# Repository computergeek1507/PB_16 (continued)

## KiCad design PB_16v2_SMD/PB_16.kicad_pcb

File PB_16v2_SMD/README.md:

# Copyright and Disclaimer
Copyright: Scott Hanson

This documentation describes Open Hardware and is licensed under the CERN Open Hardware License Version 2 - Strongly Reciprocal. (CERN-OHL-S)

You may redistribute and modify this documentation under the terms of the CERN OHL-S-v2 (https://ohwr.org/cern_ohl_s_v2.txt). This documentation is distributed WITHOUT ANY EXPRESS OR IMPLIED WARRANTY, INCLUDING OF MERCHANTABILITY, SATISFACTORY QUALITY AND FITNESS FOR A PARTICULAR PURPOSE. Please see the CERN OHL v2-S for applicable conditions

**Under CERN OHL-S-v2, derivative work must be publicly released as defined in subsection 3.3**

# PB 16v2

The PB 16v2 is a surface mount(SMD) version of the original PB16. The updated PB 16v2 has 16 local pixel ports, one remote receiver port(4 remote ports), a 16 port expansion, and 2 serial ports. A total of 36 pixel outputs. All the design files are open source and available on github.

### Features
* Powered by FPP Falcon Player
* Standalone/Master/Remote/Bridge Support
* 16 3-Wire Pixel Ports
* 1 RJ-45 Connector for a remote differential port.
* 700 pixel per output at 40 FPS or 1300 at 20 FPS
* 2 DMX Serial Outputs
* 1 RJ-45 Connectors with DMX/LOR Wiring Support
* Fused Powered DMX Output
* USB port for Ethernet,WIFI, or Audio
* OLED Display header
* Adafruit Real Time Clock Header Connector
* 2 pin GPIO Header for Push Button or Relay Support
* 5v - 24v Vin Support
* Expansion Header for additional 16 pixel outputs, Supports Falcon(v3) Expansion Boards

### Purchase
I (Scott) have a limited quantity of fully assembled PCB's available for purchase. PM me if interested.

## [Part BOM](https://github.com/computergeek1507/PB_16/raw/master/PB_16v2_SMD/PB_16_BOM.ods)

## [Interactive BOM](https://computergeek1507.github.io/PB_16/PB_16v2_SMD/bom/ibom)

----
## Changelog

v2.3
----
* 2026-02-09
* Switched to TSSOP-20 for U4 & U5.
* Switched Pixel Outputs to Dual 3.5mm/3.81mm Pads.
* Switched Expansion Header to 24pin Falcon V4 pinout.
* Removed OLED Slide Switch.
* Removed Top Solder pour.

v2.2
----
* 2022-06-05
* Updated 5V regulator to "Universal" footprint to support different regulators.
* Switched to 603 Resistors and Capacitors
* Added Logo

v2.1
----
* 2022-05-26
* Switched to surface mount 33ohm resistors on pixel outputs.

v2
----
* 2020-08-11 (publicly released 2022-01-22)
* First SMD version.
* Based off PB16v1.
* Used 805 Resistors and Capacitors
* Changed one RJ45 port to new differential output.
* Added Power Controller to USB port.
* Added TVS Diodes to USB port.

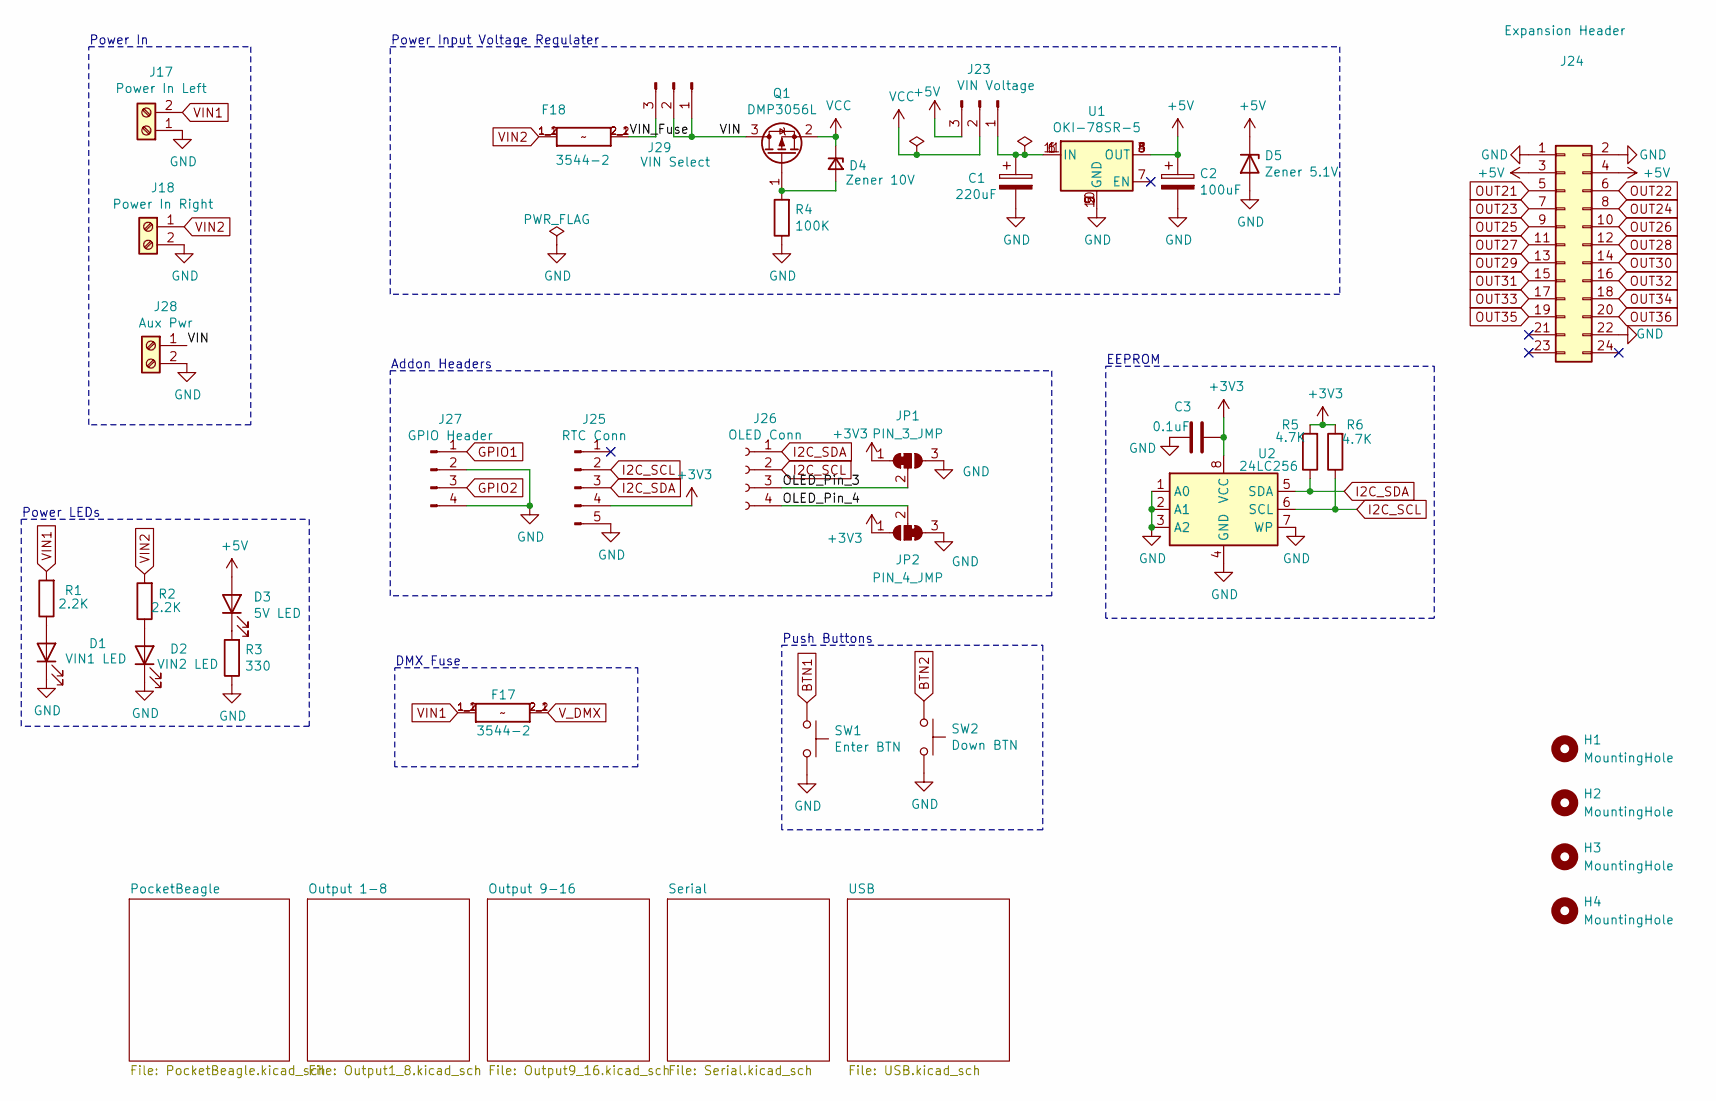
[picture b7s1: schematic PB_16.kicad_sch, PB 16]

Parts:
C1: 220uF; CP_Radial_D10.0mm_P5.00mm; MPN ECA-1HM221; Digi-Key_PN P5183-ND
C2: 100uF; CP_Elec_6.3x5.4_Nichicon; MPN UWX1C101MCL1GB; Digi-Key_PN 493-2105-1-ND
C3: 0.1uF; C_0603_1608Metric; MPN CL10B104KB8NNWC; Digi-Key_PN 1276-1935-2-ND
D1: VIN1 LED; LED_0603_1608Metric; MPN LTST-C190KRKT; Digi-Key_PN 160-1436-2-ND
D2: VIN2 LED; LED_0603_1608Metric; MPN LTST-C190KRKT; Digi-Key_PN 160-1436-2-ND
D3: 5V LED; LED_0603_1608Metric; MPN LTST-C190KRKT; Digi-Key_PN 160-1436-2-ND
D4: Zener 10V; D_SOD-123; MPN MMSZ5240B-7-F; Digi-Key_PN MMSZ5240B-FDICT-ND
D5: Zener 5.1V; D_SOD-123; MPN MMSZ5231B-7-F; Digi-Key_PN MMSZ5231B-FDICT-ND
F17, F18: 3544-2; FUSE_3544-2; MPN 3544-2; Digi-Key_PN 36-3544-2-ND
H1, H2, H3, H4: MountingHole; MountingHole_3.7mm
J17: Power In Left; BARRIER_BLOCK_1ROW_2POS_P9.5MM; MPN OSTYK51102030; Digi-Key_PN ED2953-ND
J18: Power In Right; BARRIER_BLOCK_1ROW_2POS_P9.5MM; MPN OSTYK51102030; Digi-Key_PN ED2953-ND
J23: VIN Voltage; PinHeader_1x03_P2.54mm_Vertical; MPN 61300311121; Digi-Key_PN 732-5316-ND
J24: Expansion Header; IDC-Header_2x12_P2.54mm_Vertical; MPN SBH11-PBPC-D20-ST-BK; Digi-Key_PN S9175-ND
J25: RTC Conn; PinHeader_1x05_P2.54mm_Vertical; MPN 61300511121; Digi-Key_PN 732-5318-ND
J26: OLED Conn; PinSocket_1x04_P2.54mm_Vertical; MPN PPTC041LFBN-RC; Digi-Key_PN S7002-ND
J27: GPIO Header; JST_XH_B4B-XH-A_1x04_P2.50mm_Vertical; MPN B4B-XH-A(LF)(SN); Digi-Key_PN 455-2249-ND
J28: Aux Pwr; PHOENIX_MKDS1_2-3.81; MPN 1727010; Digi-Key_PN 277-1947-ND
J29: VIN Select; PinHeader_1x03_P2.54mm_Vertical; MPN 61300311121; Digi-Key_PN 732-5316-ND
JP1: PIN_3_JMP; SolderJumper-3_P1mm_Bridged12
JP2: PIN_4_JMP; SolderJumper-3_P1mm_Bridged23
Q1: DMP3056L; SOT-23; MPN DMP3056L-7; Digi-Key_PN DMP3056L-7DICT-ND
R1, R2: 2.2K; R_0603_1608Metric; MPN RC0603FR-071KL; Digi-Key_PN 311-1.00KHRTR-ND
R3: 330; R_0603_1608Metric; MPN CRGCQ0603F120R; Digi-Key_PN A129677CT-ND
R4: 100K; R_0603_1608Metric; MPN RT0603BRD07100KL; Digi-Key_PN YAG1235CT-ND
R5, R6: 4.7K; R_0603_1608Metric; MPN RC0603JR-074K7L; Digi-Key_PN 311-4.7KGRCT-ND
SW1: Enter BTN; SW_Push_1P1T_NO_6x6mm_H9.5mm; MPN PTS645SL50SMTR92 LFS; Digi-Key_PN CKN9088CT-ND
SW2: Down BTN; SW_Push_1P1T_NO_6x6mm_H9.5mm; MPN PTS645SL50SMTR92 LFS; Digi-Key_PN CKN9088CT-ND
U1: OKI-78SR-5; Universal_5V_Horizontal; MPN OKI-78SR-5/1.5-W36-C; Digi-Key_PN 811-2196-5-ND
U2: 24LC256; SOIC-8_3.9x4.9mm_P1.27mm; MPN 24LC256T-I/SN; Digi-Key_PN 24LC256T-I/SNCT-ND

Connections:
+3V3: C3.1, J25.4, JP1.1 (A), JP2.1 (A), R5.2, R6.2, U2.8 (VCC); also elsewhere on the board
+5V: C2.1, D3.2 (A), D5.1 (K), J23.3, J24.3, J24.4, U1.3 (OUT), U1.4 (OUT), U1.8 (OUT); also elsewhere on the board
/OLED_Pin_3: J26.3, JP1.2 (C)
/OLED_Pin_4: J26.4, JP2.2 (C)
/VIN: J28.1, J29.1, J29.2, Q1.3 (D)
/VIN_Fuse: F18.2_1 (2), F18.2_2 (2), J29.3
BTN1: SW1.1; also elsewhere on the board
BTN2: SW2.1; also elsewhere on the board
GND: C1.2, C2.2, C3.2, D1.1 (K), D2.1 (K), D5.2 (A), J17.1, J18.2, J24.1, J24.2, J24.22, J25.5, J27.2, J27.4, J28.2, JP1.3 (B), JP2.3 (B), R3.1, R4.1, SW1.2, SW2.2, U1.2 (GND), U1.5 (GND), U1.9 (GND), U1.10 (GND), U2.1 (A0), U2.2 (A1), U2.3 (A2), U2.4 (GND), U2.7 (WP); also elsewhere on the board
GPIO1: J27.1; also elsewhere on the board
GPIO2: J27.3; also elsewhere on the board
I2C_SCL: J25.2, J26.2, R6.1, U2.6 (SCL); also elsewhere on the board
I2C_SDA: J25.3, J26.1, R5.1, U2.5 (SDA); also elsewhere on the board
unnamed: D1.2 (A), R1.1
unnamed: D2.2 (A), R2.1
unnamed: D3.1 (K), R3.2
unnamed: D4.2 (A), Q1.1 (G), R4.2
unnamed: C1.1, J23.1, U1.1 (IN), U1.6 (IN), U1.11 (IN)
OUT21: J24.5; also elsewhere on the board
OUT22: J24.6; also elsewhere on the board
OUT23: J24.7; also elsewhere on the board
OUT24: J24.8; also elsewhere on the board
OUT25: J24.9; also elsewhere on the board
OUT26: J24.10; also elsewhere on the board
OUT27: J24.11; also elsewhere on the board
OUT28: J24.12; also elsewhere on the board
OUT29: J24.13; also elsewhere on the board
OUT30: J24.14; also elsewhere on the board
OUT31: J24.15; also elsewhere on the board
OUT32: J24.16; also elsewhere on the board
OUT33: J24.17; also elsewhere on the board
OUT34: J24.18; also elsewhere on the board
OUT35: J24.19; also elsewhere on the board
OUT36: J24.20; also elsewhere on the board
VCC: D4.1 (K), J23.2, Q1.2 (S)
VIN1: F17.1_1 (1), F17.1_2 (1), J17.2, R1.2; also elsewhere on the board
VIN2: F18.1_1 (1), F18.1_2 (1), J18.1, R2.2; also elsewhere on the board
V_DMX: F17.2_1 (2), F17.2_2 (2); also elsewhere on the board

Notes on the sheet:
Power Input Voltage Regulater
Push Buttons
Power LEDs
EEPROM
Power In
Addon Headers
DMX Fuse

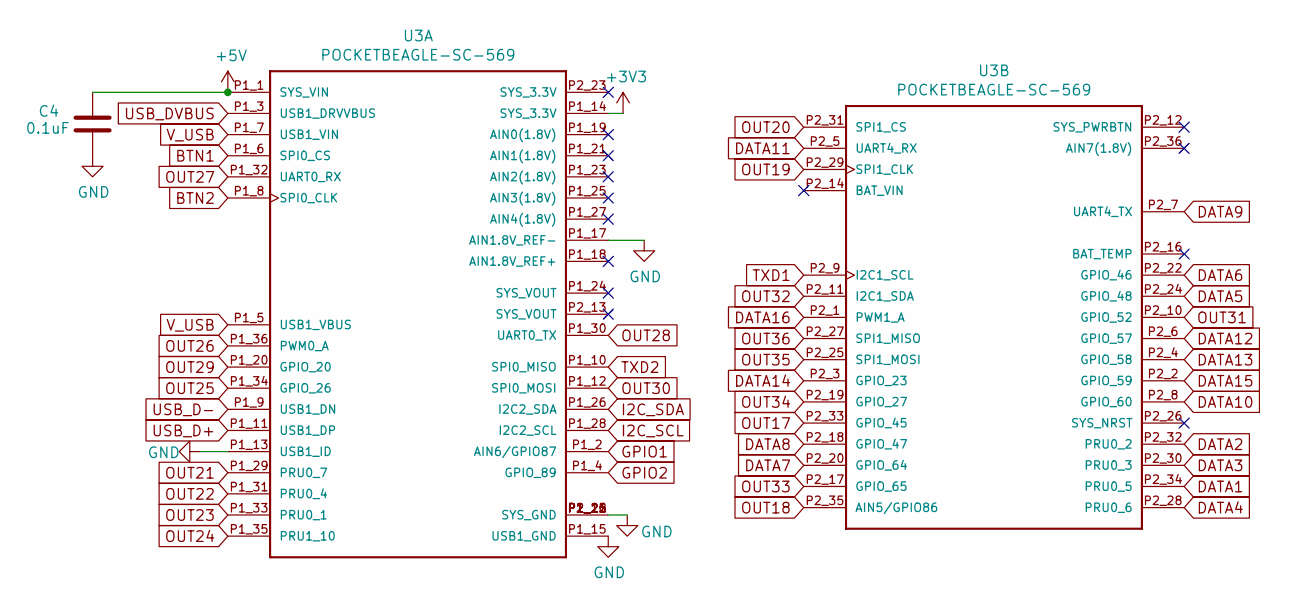
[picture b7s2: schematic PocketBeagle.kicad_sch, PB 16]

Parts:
C4: 0.1uF; C_0603_1608Metric; MPN CL10B104KB8NNWC; Digi-Key_PN 1276-1935-2-ND
U3: POCKETBEAGLE-SC-569; BEAGLE_POCKETBEAGLE-SC-569; MPN POCKETBEAGLE-SC-569; Digi-Key_PN POCKETBEAGLE-SC-569-ND

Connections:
+3V3: U3.P1_14 (SYS_3.3V); also elsewhere on the board
+5V: C4.1, U3.P1_1 (SYS_VIN); also elsewhere on the board
BTN1: U3.P1_6 (SPI0_CS); also elsewhere on the board
BTN2: U3.P1_8 (SPI0_CLK); also elsewhere on the board
DATA1: U3.P2_34 (PRU0_5); also elsewhere on the board
DATA2: U3.P2_32 (PRU0_2); also elsewhere on the board
DATA3: U3.P2_30 (PRU0_3); also elsewhere on the board
DATA4: U3.P2_28 (PRU0_6); also elsewhere on the board
DATA5: U3.P2_24 (GPIO_48); also elsewhere on the board
DATA6: U3.P2_22 (GPIO_46); also elsewhere on the board
DATA7: U3.P2_20 (GPIO_64); also elsewhere on the board
DATA8: U3.P2_18 (GPIO_47); also elsewhere on the board
DATA9: U3.P2_7 (UART4_TX); also elsewhere on the board
DATA10: U3.P2_8 (GPIO_60); also elsewhere on the board
DATA11: U3.P2_5 (UART4_RX); also elsewhere on the board
DATA12: U3.P2_6 (GPIO_57); also elsewhere on the board
DATA13: U3.P2_4 (GPIO_58); also elsewhere on the board
DATA14: U3.P2_3 (GPIO_23); also elsewhere on the board
DATA15: U3.P2_2 (GPIO_59); also elsewhere on the board
DATA16: U3.P2_1 (PWM1_A); also elsewhere on the board
GND: C4.2, U3.P1_13 (USB1_ID), U3.P1_15 (USB1_GND), U3.P1_16 (SYS_GND), U3.P1_17 (AIN1.8V_REF-), U3.P1_22 (SYS_GND), U3.P2_15 (SYS_GND), U3.P2_21 (SYS_GND); also elsewhere on the board
GPIO1: U3.P1_2 (AIN6/GPIO87); also elsewhere on the board
GPIO2: U3.P1_4 (GPIO_89); also elsewhere on the board
I2C_SCL: U3.P1_28 (I2C2_SCL); also elsewhere on the board
I2C_SDA: U3.P1_26 (I2C2_SDA); also elsewhere on the board
OUT17: U3.P2_33 (GPIO_45); also elsewhere on the board
OUT18: U3.P2_35 (AIN5/GPIO86); also elsewhere on the board
OUT19: U3.P2_29 (SPI1_CLK); also elsewhere on the board
OUT20: U3.P2_31 (SPI1_CS); also elsewhere on the board
OUT21: U3.P1_29 (PRU0_7); also elsewhere on the board
OUT22: U3.P1_31 (PRU0_4); also elsewhere on the board
OUT23: U3.P1_33 (PRU0_1); also elsewhere on the board
OUT24: U3.P1_35 (PRU1_10); also elsewhere on the board
OUT25: U3.P1_34 (GPIO_26); also elsewhere on the board
OUT26: U3.P1_36 (PWM0_A); also elsewhere on the board
OUT27: U3.P1_32 (UART0_RX); also elsewhere on the board
OUT28: U3.P1_30 (UART0_TX); also elsewhere on the board
OUT29: U3.P1_20 (GPIO_20); also elsewhere on the board
OUT30: U3.P1_12 (SPI0_MOSI); also elsewhere on the board
OUT31: U3.P2_10 (GPIO_52); also elsewhere on the board
OUT32: U3.P2_11 (I2C1_SDA); also elsewhere on the board
OUT33: U3.P2_17 (GPIO_65); also elsewhere on the board
OUT34: U3.P2_19 (GPIO_27); also elsewhere on the board
OUT35: U3.P2_25 (SPI1_MOSI); also elsewhere on the board
OUT36: U3.P2_27 (SPI1_MISO); also elsewhere on the board
TXD1: U3.P2_9 (I2C1_SCL); also elsewhere on the board
TXD2: U3.P1_10 (SPI0_MISO); also elsewhere on the board
USB_D+: U3.P1_11 (USB1_DP); also elsewhere on the board
USB_D-: U3.P1_9 (USB1_DN); also elsewhere on the board
USB_DVBUS: U3.P1_3 (USB1_DRVVBUS); also elsewhere on the board
V_USB: U3.P1_5 (USB1_VBUS), U3.P1_7 (USB1_VIN); also elsewhere on the board

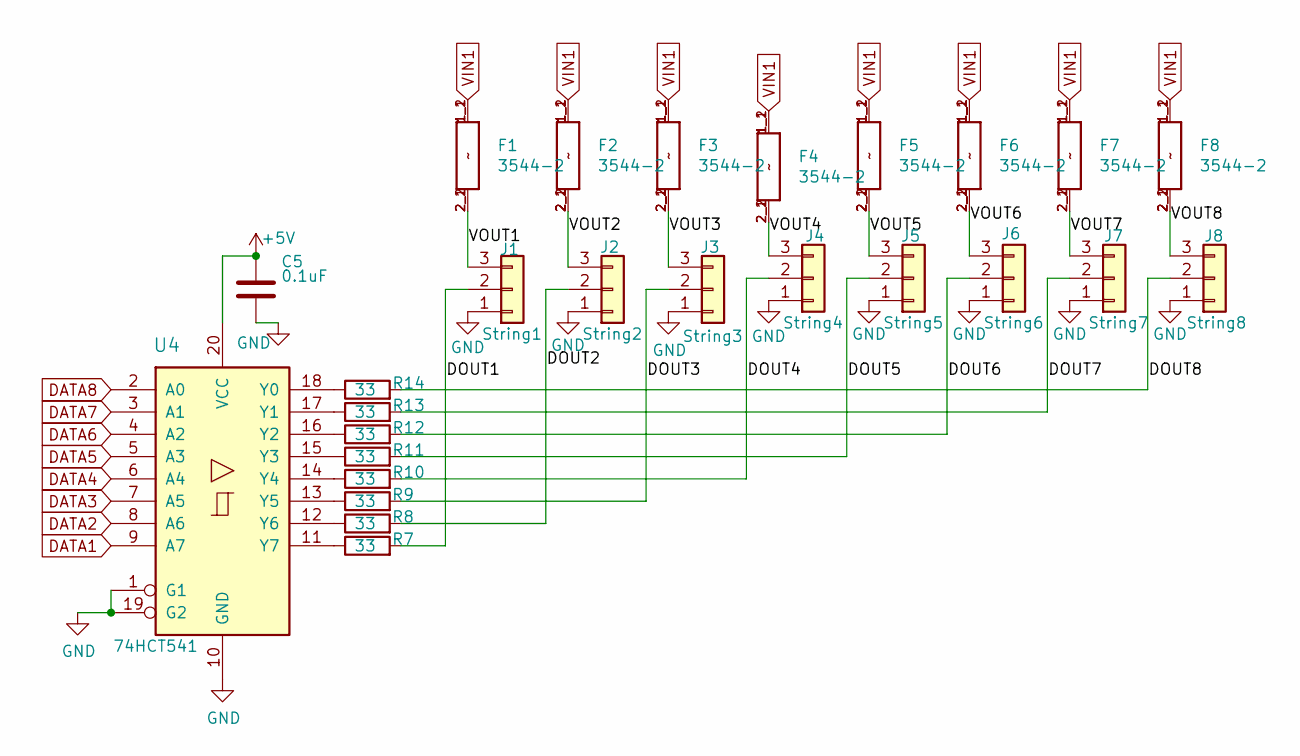
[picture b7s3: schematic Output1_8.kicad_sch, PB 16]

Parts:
C5: 0.1uF; C_0603_1608Metric; MPN CL10B104KB8NNWC; Digi-Key_PN 1276-1935-2-ND
F1, F2, F3, F4, F5, F6, F7, F8: 3544-2; FUSE_3544-2; MPN 3544-2; Digi-Key_PN 36-3544-2-ND
J1: String1; PhoenixContact_MCV_3.81mm_3.5mm_1x03_Vertical; MPN 1843619/OSTTJ0311530; Digi-Key_PN 277-5737-ND/ED10555-ND
J2: String2; PhoenixContact_MCV_3.81mm_3.5mm_1x03_Vertical; MPN 1843619/OSTTJ0311530; Digi-Key_PN 277-5737-ND/ED10555-ND
J3: String3; PhoenixContact_MCV_3.81mm_3.5mm_1x03_Vertical; MPN 1843619/OSTTJ0311530; Digi-Key_PN 277-5737-ND/ED10555-ND
J4: String4; PhoenixContact_MCV_3.81mm_3.5mm_1x03_Vertical; MPN 1843619/OSTTJ0311530; Digi-Key_PN 277-5737-ND/ED10555-ND
J5: String5; PhoenixContact_MCV_3.81mm_3.5mm_1x03_Vertical; MPN 1843619/OSTTJ0311530; Digi-Key_PN 277-5737-ND/ED10555-ND
J6: String6; PhoenixContact_MCV_3.81mm_3.5mm_1x03_Vertical; MPN 1843619/OSTTJ0311530; Digi-Key_PN 277-5737-ND/ED10555-ND
J7: String7; PhoenixContact_MCV_3.81mm_3.5mm_1x03_Vertical; MPN 1843619/OSTTJ0311530; Digi-Key_PN 277-5737-ND/ED10555-ND
J8: String8; PhoenixContact_MCV_3.81mm_3.5mm_1x03_Vertical; MPN 1843619/OSTTJ0311530; Digi-Key_PN 277-5737-ND/ED10555-ND
R7, R8, R9, R10, R11, R12, R13, R14: 33; R_0603_1608Metric; MPN RC0603FR-0733RL; Digi-Key_PN 311-33.0HRCT-ND
U4: 74HCT541; TSSOP-20_4.4x6.5mm_P0.65mm; MPN SN74HCT541PWR; Digi-Key_PN MC74HCT541ADTR2GOSTR-ND

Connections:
+5V: C5.1, U4.20 (VCC); also elsewhere on the board
/Output 1-8/DOUT1: J1.2, R7.2
/Output 1-8/DOUT2: J2.2, R8.2
/Output 1-8/DOUT3: J3.2, R9.2
/Output 1-8/DOUT4: J4.2, R10.2
/Output 1-8/DOUT5: J5.2, R11.2
/Output 1-8/DOUT6: J6.2, R12.2
/Output 1-8/DOUT7: J7.2, R13.2
/Output 1-8/DOUT8: J8.2, R14.2
/Output 1-8/VOUT1: F1.2_1 (2), F1.2_2 (2), J1.3
/Output 1-8/VOUT2: F2.2_1 (2), F2.2_2 (2), J2.3
/Output 1-8/VOUT3: F3.2_1 (2), F3.2_2 (2), J3.3
/Output 1-8/VOUT4: F4.2_1 (2), F4.2_2 (2), J4.3
/Output 1-8/VOUT5: F5.2_1 (2), F5.2_2 (2), J5.3
/Output 1-8/VOUT6: F6.2_1 (2), F6.2_2 (2), J6.3
/Output 1-8/VOUT7: F7.2_1 (2), F7.2_2 (2), J7.3
/Output 1-8/VOUT8: F8.2_1 (2), F8.2_2 (2), J8.3
DATA1: U4.9 (A7); also elsewhere on the board
DATA2: U4.8 (A6); also elsewhere on the board
DATA3: U4.7 (A5); also elsewhere on the board
DATA4: U4.6 (A4); also elsewhere on the board
DATA5: U4.5 (A3); also elsewhere on the board
DATA6: U4.4 (A2); also elsewhere on the board
DATA7: U4.3 (A1); also elsewhere on the board
DATA8: U4.2 (A0); also elsewhere on the board
GND: C5.2, J1.1, J2.1, J3.1, J4.1, J5.1, J6.1, J7.1, J8.1, U4.1 (G1), U4.10 (GND), U4.19 (G2); also elsewhere on the board
unnamed: R14.1, U4.18 (Y0)
unnamed: R13.1, U4.17 (Y1)
unnamed: R12.1, U4.16 (Y2)
unnamed: R11.1, U4.15 (Y3)
unnamed: R10.1, U4.14 (Y4)
unnamed: R9.1, U4.13 (Y5)
unnamed: R8.1, U4.12 (Y6)
unnamed: R7.1, U4.11 (Y7)
VIN1: F1.1_1 (1), F1.1_2 (1), F2.1_1 (1), F2.1_2 (1), F3.1_1 (1), F3.1_2 (1), F4.1_1 (1), F4.1_2 (1), F5.1_1 (1), F5.1_2 (1), F6.1_1 (1), F6.1_2 (1), F7.1_1 (1), F7.1_2 (1), F8.1_1 (1), F8.1_2 (1); also elsewhere on the board

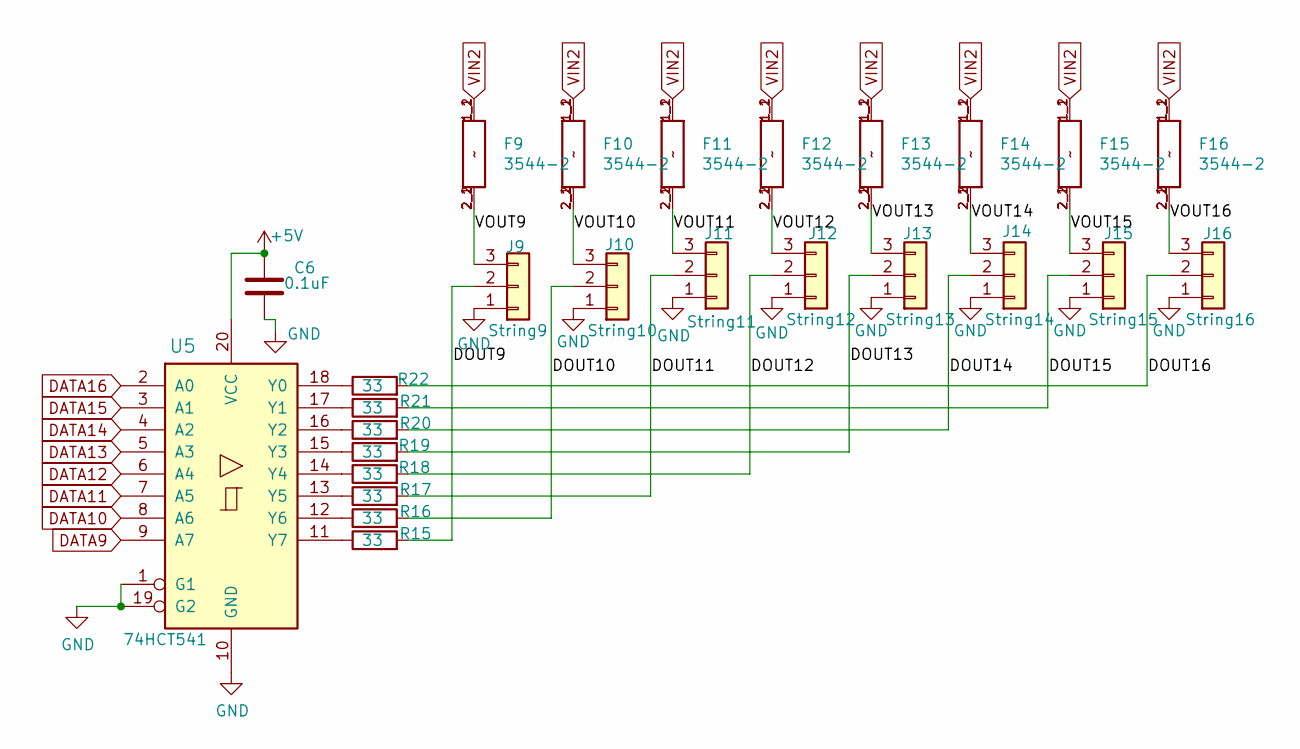
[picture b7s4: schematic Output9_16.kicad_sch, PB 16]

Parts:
C6: 0.1uF; C_0603_1608Metric; MPN CL10B104KB8NNWC; Digi-Key_PN 1276-1935-2-ND
F9, F10, F11, F12, F13, F14, F15, F16: 3544-2; FUSE_3544-2; MPN 3544-2; Digi-Key_PN 36-3544-2-ND
J9: String9; PhoenixContact_MCV_3.81mm_3.5mm_1x03_Vertical; MPN 1843619/OSTTJ0311530; Digi-Key_PN 277-5737-ND/ED10555-ND
J10: String10; PhoenixContact_MCV_3.81mm_3.5mm_1x03_Vertical; MPN 1843619/OSTTJ0311530; Digi-Key_PN 277-5737-ND/ED10555-ND
J11: String11; PhoenixContact_MCV_3.81mm_3.5mm_1x03_Vertical; MPN 1843619/OSTTJ0311530; Digi-Key_PN 277-5737-ND/ED10555-ND
J12: String12; PhoenixContact_MCV_3.81mm_3.5mm_1x03_Vertical; MPN 1843619/OSTTJ0311530; Digi-Key_PN 277-5737-ND/ED10555-ND
J13: String13; PhoenixContact_MCV_3.81mm_3.5mm_1x03_Vertical; MPN 1843619/OSTTJ0311530; Digi-Key_PN 277-5737-ND/ED10555-ND
J14: String14; PhoenixContact_MCV_3.81mm_3.5mm_1x03_Vertical; MPN 1843619/OSTTJ0311530; Digi-Key_PN 277-5737-ND/ED10555-ND
J15: String15; PhoenixContact_MCV_3.81mm_3.5mm_1x03_Vertical; MPN 1843619/OSTTJ0311530; Digi-Key_PN 277-5737-ND/ED10555-ND
J16: String16; PhoenixContact_MCV_3.81mm_3.5mm_1x03_Vertical; MPN 1843619/OSTTJ0311530; Digi-Key_PN 277-5737-ND/ED10555-ND
R15, R16, R17, R18, R19, R20, R21, R22: 33; R_0603_1608Metric; MPN RC0603FR-0733RL; Digi-Key_PN 311-33.0HRCT-ND
U5: 74HCT541; TSSOP-20_4.4x6.5mm_P0.65mm; MPN SN74HCT541PWR; Digi-Key_PN MC74HCT541ADTR2GOSTR-ND

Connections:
+5V: C6.1, U5.20 (VCC); also elsewhere on the board
/Output 9-16/DOUT9: J9.2, R15.2
/Output 9-16/DOUT10: J10.2, R16.2
/Output 9-16/DOUT11: J11.2, R17.2
/Output 9-16/DOUT12: J12.2, R18.2
/Output 9-16/DOUT13: J13.2, R19.2
/Output 9-16/DOUT14: J14.2, R20.2
/Output 9-16/DOUT15: J15.2, R21.2
/Output 9-16/DOUT16: J16.2, R22.2
/Output 9-16/VOUT9: F9.2_1 (2), F9.2_2 (2), J9.3
/Output 9-16/VOUT10: F10.2_1 (2), F10.2_2 (2), J10.3
/Output 9-16/VOUT11: F11.2_1 (2), F11.2_2 (2), J11.3
/Output 9-16/VOUT12: F12.2_1 (2), F12.2_2 (2), J12.3
/Output 9-16/VOUT13: F13.2_1 (2), F13.2_2 (2), J13.3
/Output 9-16/VOUT14: F14.2_1 (2), F14.2_2 (2), J14.3
/Output 9-16/VOUT15: F15.2_1 (2), F15.2_2 (2), J15.3
/Output 9-16/VOUT16: F16.2_1 (2), F16.2_2 (2), J16.3
DATA9: U5.9 (A7); also elsewhere on the board
DATA10: U5.8 (A6); also elsewhere on the board
DATA11: U5.7 (A5); also elsewhere on the board
DATA12: U5.6 (A4); also elsewhere on the board
DATA13: U5.5 (A3); also elsewhere on the board
DATA14: U5.4 (A2); also elsewhere on the board
DATA15: U5.3 (A1); also elsewhere on the board
DATA16: U5.2 (A0); also elsewhere on the board
GND: C6.2, J9.1, J10.1, J11.1, J12.1, J13.1, J14.1, J15.1, J16.1, U5.1 (G1), U5.10 (GND), U5.19 (G2); also elsewhere on the board
unnamed: R22.1, U5.18 (Y0)
unnamed: R21.1, U5.17 (Y1)
unnamed: R20.1, U5.16 (Y2)
unnamed: R19.1, U5.15 (Y3)
unnamed: R18.1, U5.14 (Y4)
unnamed: R17.1, U5.13 (Y5)
unnamed: R16.1, U5.12 (Y6)
unnamed: R15.1, U5.11 (Y7)
VIN2: F9.1_1 (1), F9.1_2 (1), F10.1_1 (1), F10.1_2 (1), F11.1_1 (1), F11.1_2 (1), F12.1_1 (1), F12.1_2 (1), F13.1_1 (1), F13.1_2 (1), F14.1_1 (1), F14.1_2 (1), F15.1_1 (1), F15.1_2 (1), F16.1_1 (1), F16.1_2 (1); also elsewhere on the board

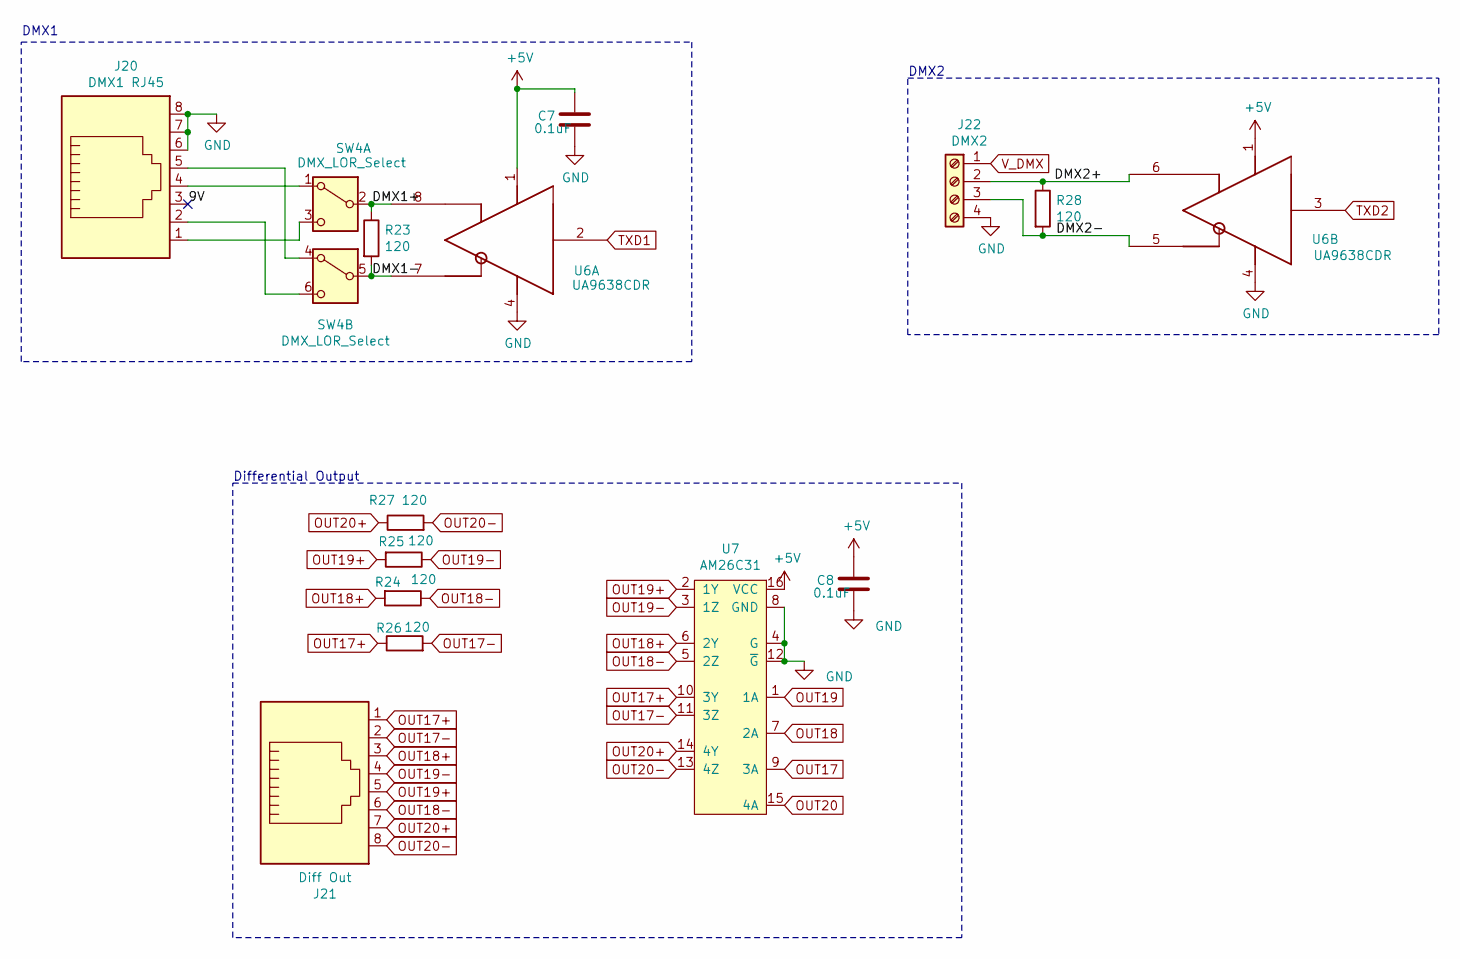
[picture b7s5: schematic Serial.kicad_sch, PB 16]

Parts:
C7, C8: 0.1uF; C_0603_1608Metric; MPN CL10B104KB8NNWC; Digi-Key_PN 1276-1935-2-ND
J20: DMX1 RJ45; RJ45_Amphenol_54602-x08_Horizontal; MPN X05ADIWA1DY1022; Digi-Key_PN AE10392-ND
J21: Diff Out; RJ45_Amphenol_54602-x08_Horizontal; MPN X05ADIWA1DY1022; Digi-Key_PN AE10392-ND
J22: DMX2; TerminalBlock_Phoenix_MKDS-1,5-4_1x04_P5.00mm_Horizontal; MPN 1729034; Digi-Key_PN 277-1238-ND
R23, R24, R25, R26, R27, R28: 120; R_0603_1608Metric; MPN CRGCQ0603F120R; Digi-Key_PN A129677CT-ND
SW4: DMX_LOR_Select; SW_CK_JS202011CQN_DPDT_Straight; MPN K3-2235D-F1; LCSC C189615
U6: UA9638CDR; SOIC-8_3.9x4.9mm_P1.27mm; MPN UA9638CDR; Digi-Key_PN 296-15058-1-ND
U7: AM26C31; SOIC-16_3.9x9.9mm_P1.27mm; MPN AM26C31IDR; Farnell 4975637

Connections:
+5V: C7.1, C8.1, U6.1 (VCC), U7.16 (VCC); also elsewhere on the board
/Serial/9V: J20.3
/Serial/DMX1+: R23.1, SW4.2 (B), U6.8 (OUTB)
/Serial/DMX1-: R23.2, SW4.5 (B), U6.7 (OUTA)
/Serial/DMX2+: J22.2, R28.1, U6.6 (OUTB)
/Serial/DMX2-: J22.3, R28.2, U6.5 (OUTA)
GND: C7.2, C8.2, J20.6, J20.7, J20.8, J22.4, U6.4 (GND), U7.4 (G), U7.8 (GND), U7.12 (~G); also elsewhere on the board
unnamed: J20.4, SW4.1 (A)
unnamed: J20.1, SW4.3 (C)
unnamed: J20.5, SW4.4 (A)
unnamed: J20.2, SW4.6 (C)
OUT17: U7.9 (3A); also elsewhere on the board
OUT17+: J21.1, R26.1, U7.10 (3Y)
OUT17-: J21.2, R26.2, U7.11 (3Z)
OUT18: U7.7 (2A); also elsewhere on the board
OUT18+: J21.3, R24.2, U7.6 (2Y)
OUT18-: J21.6, R24.1, U7.5 (2Z)
OUT19: U7.1 (1A); also elsewhere on the board
OUT19+: J21.5, R25.2, U7.2 (1Y)
OUT19-: J21.4, R25.1, U7.3 (1Z)
OUT20: U7.15 (4A); also elsewhere on the board
OUT20+: J21.7, R27.1, U7.14 (4Y)
OUT20-: J21.8, R27.2, U7.13 (4Z)
TXD1: U6.2 (IN); also elsewhere on the board
TXD2: U6.3 (IN); also elsewhere on the board
V_DMX: J22.1; also elsewhere on the board

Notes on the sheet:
Differential Output
DMX2
DMX1

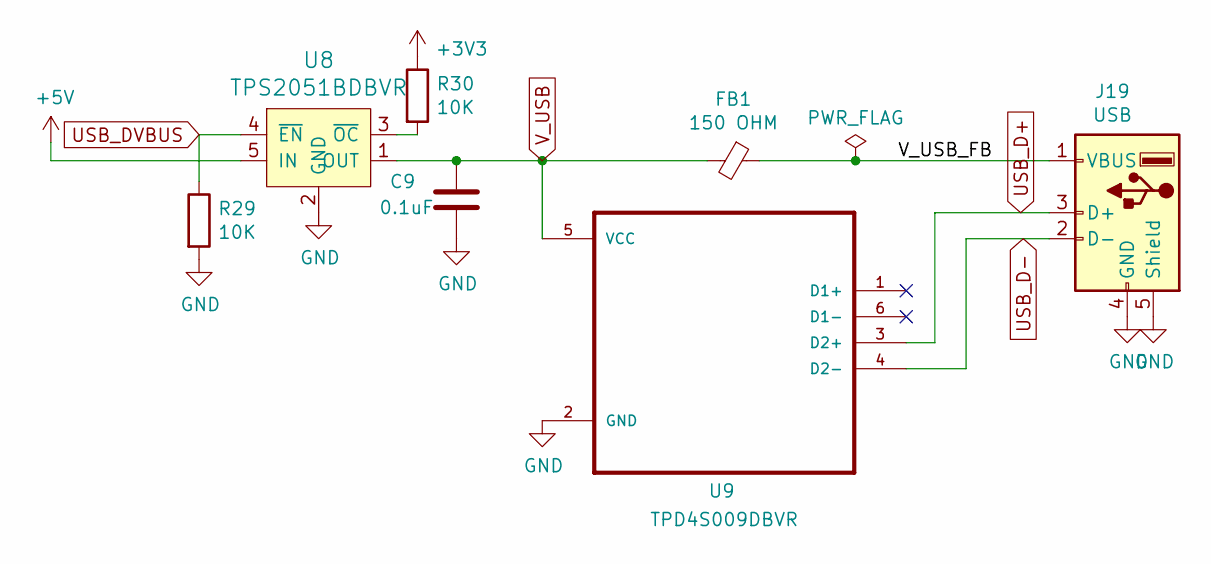
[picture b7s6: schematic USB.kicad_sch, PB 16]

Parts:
C9: 0.1uF; C_0603_1608Metric; MPN CL10B104KB8NNWC; Digi-Key_PN 1276-1935-2-ND
FB1: 150 OHM; L_0805_2012Metric; MPN MU2029-151Y; Digi-Key_PN MU2029-151YCT-ND
J19: USB; USB_A_Molex_105057_Vertical; MPN 1050570001; Digi-Key_PN WM8672-ND
R29, R30: 10K; R_0603_1608Metric; MPN RC0603FR-0710KL; Digi-Key_PN 311-10.0KHRCT-ND
U8: TPS2051BDBVR; SOT-753; MPN TPS2051BDBVR; Digi-Key_PN 296-21265-1-ND
U9: TPD4S009DBVR; SOT-23-6_Handsoldering; MPN TPD4S009DBVR; Digi-Key_PN 296-23749-1-ND

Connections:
+3V3: R30.1; also elsewhere on the board
+5V: U8.5 (IN); also elsewhere on the board
/USB/V_USB_FB: FB1.1, J19.1 (VBUS)
GND: C9.2, J19.4 (GND), J19.5 (Shield), R29.2, U8.2 (GND), U9.2 (GND); also elsewhere on the board
unnamed: R30.2, U8.3 (~OC)
USB_D+: J19.3 (D+), U9.3 (D2+); also elsewhere on the board
USB_D-: J19.2 (D-), U9.4 (D2-); also elsewhere on the board
USB_DVBUS: R29.1, U8.4 (~EN); also elsewhere on the board
V_USB: C9.1, FB1.2, U8.1 (OUT), U9.5 (VCC); also elsewhere on the board

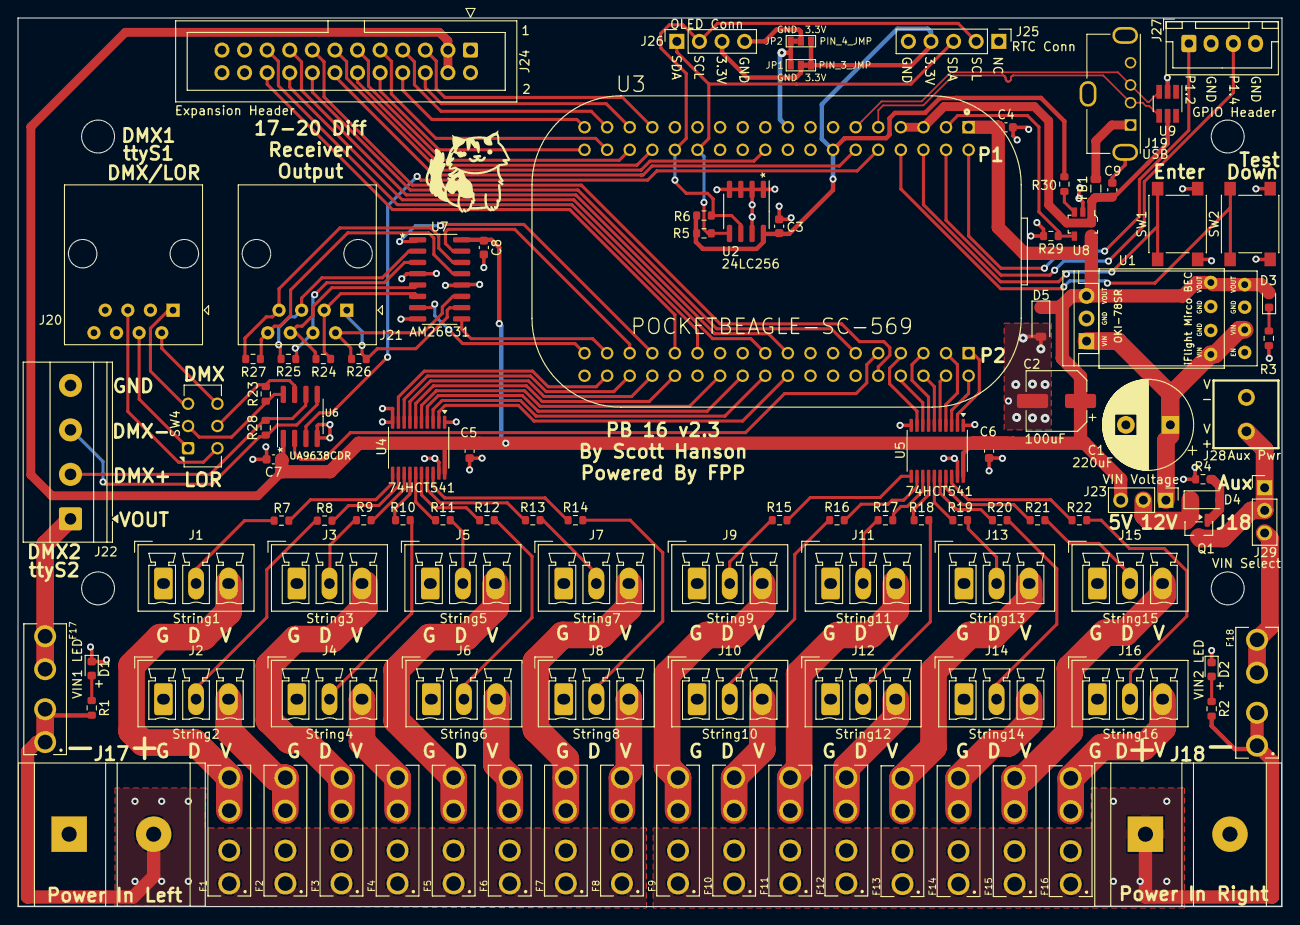
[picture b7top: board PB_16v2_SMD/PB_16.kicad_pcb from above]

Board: 2 copper layers, 142.1 x 99.9 mm, 111 parts (0 on the bottom side), 130 nets.

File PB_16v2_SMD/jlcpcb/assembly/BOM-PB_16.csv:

Comment,Designator,Footprint,LCSC
150 OHM,FB1,L_0805_2012Metric_Pad1.15x1.40mm_HandSolder,C1015
Enter BTN,"SW1,SW2",SW_Push_1P1T_NO_6x6mm_H9.5mm,C127509
SN74HCT245N,"U4,U5",SN74HCT245NSR,C133641
100uF,C2,CP_Elec_6.3x5.4_Nichicon,C134723
GPIO Header,J27,JST_XH_B4B-XH-A_1x04_P2.50mm_Vertical,C144395
0.1uF,"C3,C4,C5,C6,C7,C8,C9",C_0603_1608Metric_Pad1.08x0.95mm_HandSolder,C14663
DMP3056L,Q1,SOT-23,C150724
AM26C31,U7,SOIC-16_3.9x9.9mm_P1.27mm,C157476
Zener 5.1V,D5,D_SOD-123,C173407
Zener 10V,D4,D_SOD-123,C173431
OLED Select,"SW3,SW4",SW_CuK_JS202011CQN_DPDT_Straight,C189615
DMX2,J22,"TerminalBlock_Phoenix_MKDS-1,5-4_1x04_P5.00mm_Horizontal",C192769
String1,"J1,J10,J11,J12,J13,J14,J15,J16,J2,J3,J4,J5,J6,J7,J8,J9","PhoenixContact_MCV_1,5_3-G-3.5_1x03_P3.50mm_Vertical",C192778
1K,"R1,R2",R_0603_1608Metric_Pad0.98x0.95mm_HandSolder,C21190
OLED Conn,J26,PinSocket_1x04_P2.54mm_Vertical,C225501
120,"R23,R24,R25,R26,R27,R28,R3",R_0603_1608Metric_Pad0.98x0.95mm_HandSolder,C22787
VIN1 LED,"D1,D2,D3",LED_0603_1608Metric_Pad1.05x0.95mm_HandSolder,C2286
33,"R10,R11,R12,R13,R14,R15,R16,R17,R18,R19,R20,R21,R22,R7,R8,R9",R_0603_1608Metric_Pad0.98x0.95mm_HandSolder,C23140
4.7K,"R5,R6",R_0603_1608Metric_Pad0.98x0.95mm_HandSolder,C23162
TPS2051BDBVR,U8,SOT-753,C24593
100K,R4,R_0603_1608Metric_Pad0.98x0.95mm_HandSolder,C25803
10K,"R29,R30",R_0603_1608Metric_Pad0.98x0.95mm_HandSolder,C25804
DMX1 RJ45,"J20,J21",RJ45_Amphenol_54602-x08_Horizontal,C2938579
220uF,C1,CP_Radial_D10.0mm_P5.00mm,C338228
RTC Conn,J25,PinHeader_1x05_P2.54mm_Vertical,C358687
USB,J19,USB_A_Molex_105057_Vertical,C39455
UA9638CDR,U6,SOIC-8_3.9x4.9mm_P1.27mm,C435812
VIN Voltage,"J23,J29",PinHeader_1x03_P2.54mm_Vertical,C49257
3544-2,"F1,F10,F11,F12,F13,F14,F15,F16,F17,F18,F2,F3,F4,F5,F6,F7,F8,F9",FUSE_3544-2,C492610
24LC256,U2,SOIC-8_3.9x4.9mm_P1.27mm,C6482
Aux Pwr,J28,PHOENIX_MKDS1_2-3.81,C69811
Power In Left,"J17,J18",BARRIER_BLOCK_1ROW_2POS_P9.5MM,C707421
TPD4S009DBVR,U9,SOT-23-6_Handsoldering,C88032
Expansion Header,J24,IDC-Header_2x20_P2.54mm_Vertical,C9138
OKI-78SR-5,U1,Universal_5V_Horizontal,
POCKETBEAGLE-SC-569,U3,BEAGLE_POCKETBEAGLE-SC-569,
